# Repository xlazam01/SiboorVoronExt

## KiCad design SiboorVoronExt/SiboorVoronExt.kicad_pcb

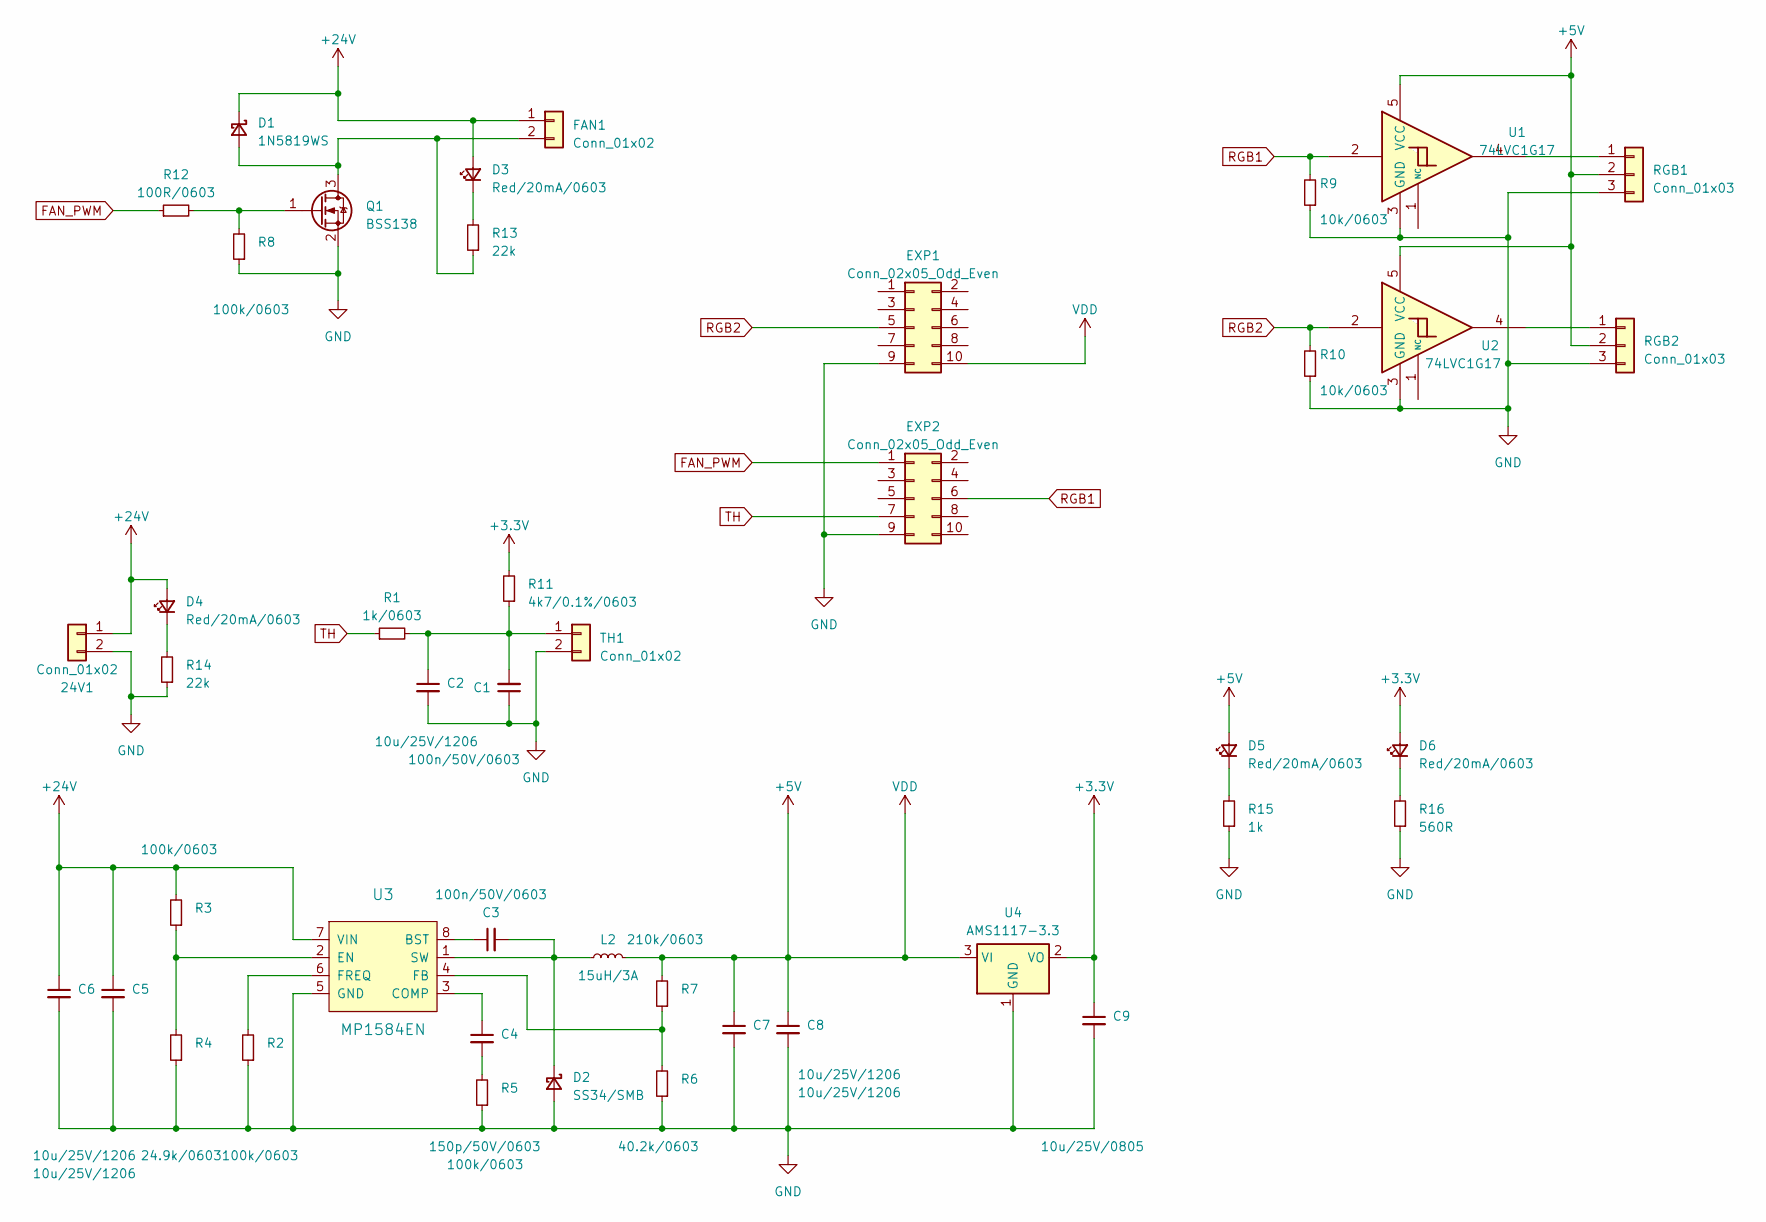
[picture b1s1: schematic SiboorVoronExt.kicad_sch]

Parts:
24V1: Conn_01x02; JST_XH_B2B-XH-A_1x02_P2.50mm_Vertical
C1, C3: 100n/50V/0603; C_0603_1608Metric_Pad1.08x0.95mm_HandSolder
C2, C7: 10u/25V/1206; C_1206_HandSolder
C4: 150p/50V/0603; C_0603_1608Metric_Pad1.08x0.95mm_HandSolder
C5, C6: 10u/25V/1206; C_1206_3216Metric_Pad1.33x1.80mm_HandSolder
C8: 10u/25V/1206; R_0805_2012Metric_Pad1.20x1.40mm_HandSolder
C9: 10u/25V/0805; C_0805_2012Metric_Pad1.18x1.45mm_HandSolder
D1: 1N5819WS; D_SOD-123
D2: SS34/SMB; D_SMB_Handsoldering
D3, D4, D5, D6: Red/20mA/0603; LED_0603_1608Metric_Pad1.05x0.95mm_HandSolder
EXP1, EXP2: Conn_02x05_Odd_Even; PinHeader_2x05_P2.54mm_Vertical
FAN1: Conn_01x02; JST_XH_B2B-XH-A_1x02_P2.50mm_Vertical
L2: 15uH/3A; L_8.0x7.5
Q1: BSS138; SOT-23_Handsoldering
R1: 1k/0603; R_0603_1608Metric_Pad0.98x0.95mm_HandSolder
R2, R3, R5, R8: 100k/0603; R_0603_1608Metric_Pad0.98x0.95mm_HandSolder
R4: 24.9k/0603; R_0603_1608Metric_Pad0.98x0.95mm_HandSolder
R6: 40.2k/0603; R_0805_2012Metric_Pad1.20x1.40mm_HandSolder
R7: 210k/0603; R_0805_2012Metric_Pad1.20x1.40mm_HandSolder
R9, R10: 10k/0603; R_0603_1608Metric_Pad0.98x0.95mm_HandSolder
R11: 4k7/0.1%/0603; R_0603_1608Metric_Pad0.98x0.95mm_HandSolder
R12: 100R/0603; R_0603_1608Metric_Pad0.98x0.95mm_HandSolder
R13, R14: 22k; R_0603_1608Metric_Pad0.98x0.95mm_HandSolder
R15: 1k; R_0603_1608Metric_Pad0.98x0.95mm_HandSolder
R16: 560R; R_0603_1608Metric_Pad0.98x0.95mm_HandSolder
RGB1, RGB2: Conn_01x03; JST_XH_B3B-XH-A_1x03_P2.50mm_Vertical
TH1: Conn_01x02; JST_XH_B2B-XH-A_1x02_P2.50mm_Vertical
U1, U2: 74LVC1G17; SOT-23-5_HandSoldering
U3: MP1584EN; SOIC-8-1EP_3.9x4.9mm_P1.27mm_EP2.29x3mm_ThermalVias
U4: AMS1117-3.3; SOT-223-3_TabPin2

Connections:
+3.3V: C9.1, D6.2 (A), R11.2, U4.2 (VO)
+5V: C7.1, C8.1, D5.2 (A), EXP1.10, L2.2, R7.2, RGB1.2, RGB2.2, U1.5 (VCC), U2.5 (VCC), U4.3 (VI)
+24V: 24V1.1, C5.1, C6.1, D1.1 (K), D3.2 (A), D4.2 (A), FAN1.1, R3.2, U3.7 (VIN)
FAN_PWM: EXP2.1, R12.1
GND: 24V1.2, C1.1, C2.2, C5.2, C6.2, C7.2, C8.2, C9.2, D2.2 (A), EXP1.9, EXP2.9, Q1.2 (S), R2.1, R4.1, R5.1, R6.1, R8.1, R9.1, R10.1, R14.1, R15.1, R16.1, RGB1.3, RGB2.3, TH1.2, U1.3 (GND), U2.3 (GND), U3.5 (GND), U3.9 (EP), U4.1 (GND)
unnamed: C4.2, R5.2
unnamed: D1.2 (A), FAN1.2, Q1.3 (D), R13.1
unnamed: C3.2, D2.1 (K), L2.1, U3.1 (SW)
unnamed: D3.1 (K), R13.2
unnamed: D4.1 (K), R14.2
unnamed: D5.1 (K), R15.2
unnamed: D6.1 (K), R16.2
unnamed: Q1.1 (G), R8.2, R12.2
unnamed: RGB1.1, U1.4
unnamed: RGB2.1, U2.4
unnamed: C1.2, C2.1, R1.2, R11.1, TH1.1
unnamed: C3.1, U3.8 (BST)
unnamed: C4.1, U3.3 (COMP)
unnamed: R3.1, R4.2, U3.2 (EN)
unnamed: R6.2, R7.1, U3.4 (FB)
unnamed: R2.2, U3.6 (FREQ)
RGB1: EXP2.6, R9.2, U1.2
RGB2: EXP1.5, R10.2, U2.2
TH: EXP2.7, R1.1

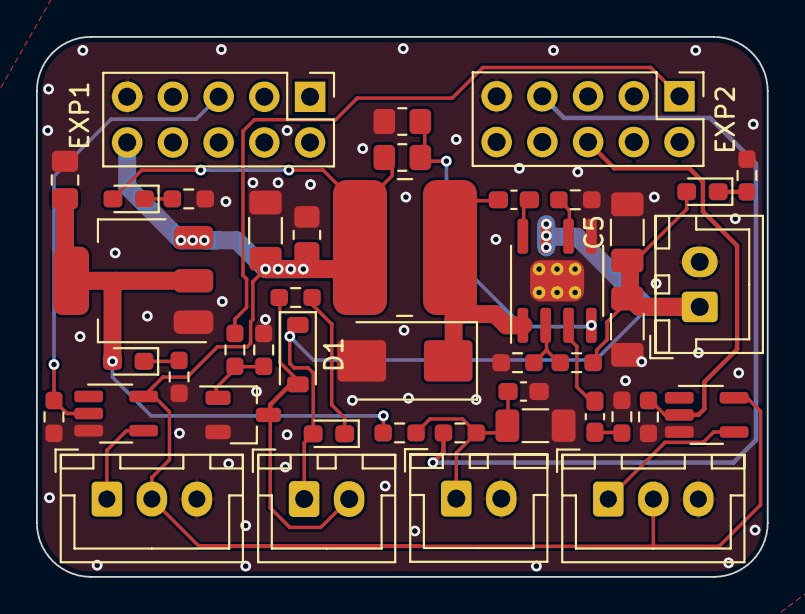
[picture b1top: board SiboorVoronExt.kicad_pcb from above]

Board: 2 copper layers, 40.6 x 30.0 mm, 44 parts (0 on the bottom side), 24 nets.

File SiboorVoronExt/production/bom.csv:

Designator,Footprint,Quantity,Value,LCSC Part #
"24V1, FAN1, TH1",JST_XH_B2B-XH-A_1x02_P2.50mm_Vertical,3,Conn_01x02,
"C1, C3",0603,2,100n/50V/0603,
"C2, C5, C6, C7, C8, C9",0805,6,10u/25V/0805,
C4,0603,1,150p/50V/0603,
D1,D_SOD-323,1,1N5819WS,
D2,D_SMB_Handsoldering,1,SS34/SMB,
"D3, D4, D5, D6",0603,4,Red/20mA/0603,
"EXT1, EXT2",PinHeader_2x05_P2.54mm_Vertical,2,Conn_02x05_Odd_Even,
JP1,SolderJumper-2_P1.3mm_Open_RoundedPad1.0x1.5mm,1,SolderJumper_2_Open,
L2,L_Wuerth_WE-PD2-Typ-L,1,15uH/3A,
Q1,SOT-23_Handsoldering,1,BSS138,
R1,0603,1,1k/0603,
"R10, R9",0603,2,10k/0603,
R11,0603,1,4k7/0.1%/0603,
R12,0603,1,100R/0603,
"R13, R14",0603,2,22k,
R15,0603,1,1k,
R16,0603,1,560R,
"R2, R3, R5, R8",0603,4,100k/0603,
R4,0603,1,24.9k/0603,
R6,0603,1,40.2k/0603,
R7,0603,1,210k/0603,
"RGB1, RGB2",JST_XH_B3B-XH-A_1x03_P2.50mm_Vertical,2,Conn_01x03,
"U1, U2",SOT-23-5_HandSoldering,2,74LVC1G17,
U3,SOIC-8-1EP_3.9x4.9mm_P1.27mm_EP2.29x3mm_ThermalVias,1,MP1584EN,
U4,SOT-223-3_TabPin2,1,AMS1117-3.3,

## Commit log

2023-07-14 First Placement
2023-07-14 Frist PCB Draft
2023-07-14 V1.0
2023-08-11 ujpdate
